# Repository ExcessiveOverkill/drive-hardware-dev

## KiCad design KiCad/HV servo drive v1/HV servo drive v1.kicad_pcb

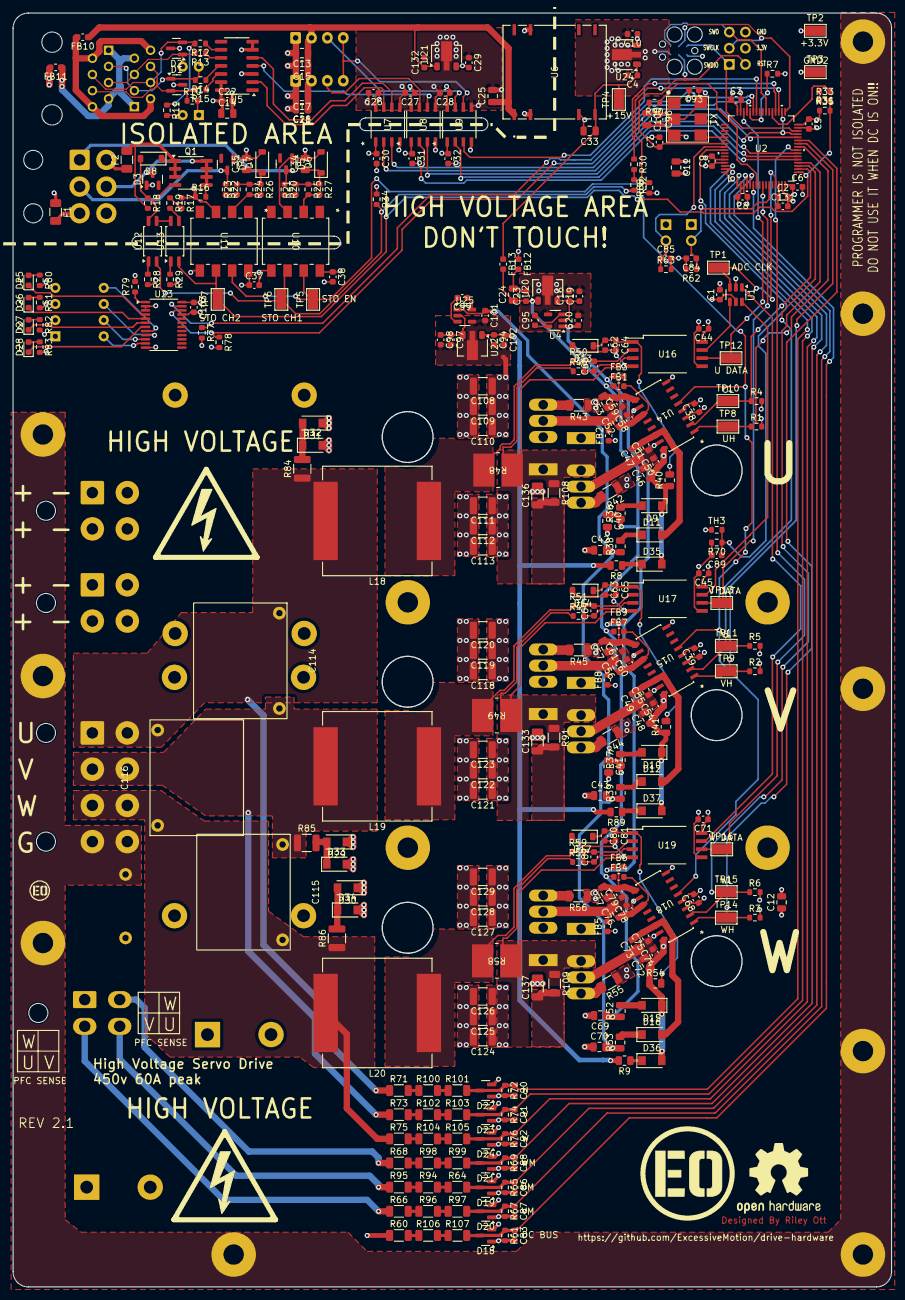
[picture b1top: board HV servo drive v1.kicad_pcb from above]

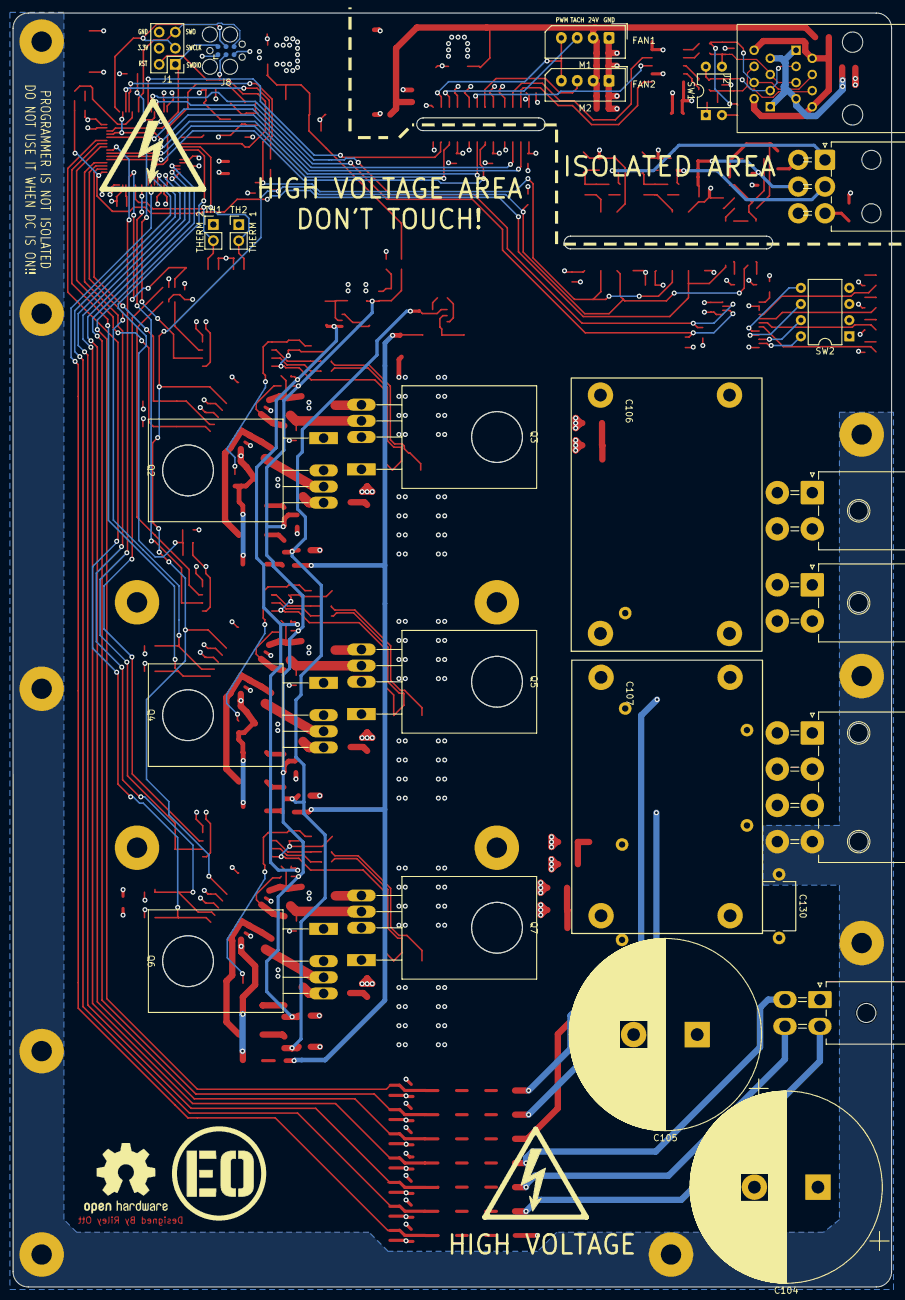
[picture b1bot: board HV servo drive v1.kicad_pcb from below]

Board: 4 copper layers, 138.2 x 200.4 mm, 371 parts (25 on the bottom side), 197 nets.

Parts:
C1, C3, C4, C5, C6, C7, C8, C9, C10, C16, C22, C23, C26, C27, C28, C29, C30, C31, C32, C36, C37, C38, C39, C44, C45, C50, C51, C54, C55, C58, C59, C60, C61, C64, C65, C68, C71, C74, C75, C78, C79, C81, C83, C86, C87, C88, C90, C91, C92, C93, C94, C96, C97, C103, C132: 0.1uf; C_0603_1608Metric
C2, C19, C20, C62, C63, C80, C84, C85, C89, C95, C98, C99, C101, C102, C131: 1uf; C_0603_1608Metric
C11, C12, C13, C14, C15, C17, C18, C21, C24, C25, C33, C34, C35, C40, C41, C42, C43, C46, C47, C48, C49, C52, C53, C56, C57, C69, C70, C72, C73, C76, C77, C100: 10uf; C_0805_2012Metric
C66, C67, C82: C; C_0603_1608Metric
C104, C105: 470uf; CP_Radial_D30.0mm_P10.00mm_SnapIn
C106, C107: 40uf; BUS CAP1
C108, C109, C110, C111, C112, C113, C118, C119, C120, C121, C122, C123, C124, C125, C126, C127, C128, C129: 47nf; C_1210_3225Metric
C114, C115, C116: 390pf; B326712L-SMD
C130: 220pf; C_Disc_D7.5mm_W5.0mm_P10.00mm
C133, C136, C137: 470pf; C_1206_3216Metric
D1, D2: SM712; SOT-23
D3, D4, D5, D18, D19, D20, D21, D22, D23, D24: BAT54SLT1G; SOT-23
D6, D7, D8, D13, D14, D17: BZT52C5V1; D_SOD-123
D9, D10, D11, D12, D15, D16, D29, D30, D31, D32, D33, D34, D35, D36, D37: RS1MLW; D_SOD-123W
D25, D26, D27, D28: LED; LED_0603_1608Metric
F1, F2: Polyfuse; Fuse_1206_3216Metric
FB1, FB2, FB3, FB4, FB5, FB6, FB7, FB8, FB9, FB10, FB11, FB12, FB13: 120 ohm; L_0603_1608Metric
H1, H2, H3, H4, H5, H6, H7, H8, H9, H10, H11, H12, H13: MountingHole; MountingHole_3.2mm_M3_Pad_TopBottom_LargeIsolation
J1: PROG; PinHeader_2x03_P2.54mm_Vertical
J2: E5908-0T0343-L; RJ45_E5908-0T0343-L
J3: STO; Molex_Mini-Fit_Jr_0455580003_2x03_P4.20mm_Horizontal
J4: PFC SENSE; Molex_Mini-Fit_Jr_5569-04A2_2x02_P4.20mm_Horizontal
J5: MOTOR; Molex_Mega-Fit_76825-0008_2x04_P5.70mm_Horizontal
J6, J7: DC BUS; Molex_Mega-Fit_76825-0004_2x02_P5.70mm_Horizontal
J8: Conn_ARM_SWD_TagConnect_TC2030; Tag-Connect_TC2030-IDC-FP_2x03_P1.27mm_Vertical
L18, L19, L20: 3.3uH; L_Vishay_IHLP-6767
M1, M2: Fan_4pin; Molex_SPOX_5267-04A_1x04_P2.50mm_Vertical
Q1: AO4421; SOIC-8_3.9x4.9mm_P1.27mm
Q2, Q3, Q4, Q5, Q6, Q7: G3R30MT12K; TO-247-4_Horizontal_TabUp
R1, R2, R3, R4, R5, R6, R7, R16, R18, R30, R31, R32, R33, R61, R62, R63, R65, R67, R69, R70, R72, R74, R76, R77, R78, R79, R88: 10k; R_0603_1608Metric
R8, R9, R36, R37, R38, R39, R52, R53, R89: 1; R_0805_2012Metric
R10, R11: 120; R_0603_1608Metric
R12, R13, R14, R15: 10; R_0603_1608Metric
R17, R19, R20, R21, R22, R23, R24, R25, R26, R27, R34, R35, R80, R81, R82, R83, R90: 1k; R_0603_1608Metric
R28, R29: 220; R_0603_1608Metric
R40, R41, R54: 820; R_0805_2012Metric
R42, R43, R44, R45, R55, R56, R91, R108, R109: 10; R_1206_3216Metric
R46, R47, R50, R51, R57, R59: 0; R_0603_1608Metric
R48, R49, R58: .005; RES_HCSM2818_STP
R60, R64, R66, R68, R71, R73, R75, R94, R95, R96, R97, R98, R99, R100, R101, R102, R103, R104, R105, R106, R107: 750k; R_1206_3216Metric
R84, R85, R86: 20; R_1210_3225Metric
SW1: DS01-254-L-02BE; DIP-4_W7.62mm
SW2: DS02C-254-1L-04BE; DIP-8_W7.62mm
TH1, TH2: Thermistor; PinHeader_1x02_P2.54mm_Vertical
TH3: Thermistor; R_0603_1608Metric
TP1, TP2, TP3, TP4, TP5, TP6, TP7, TP8, TP9, TP10, TP11, TP12, TP13, TP14, TP15, TP16: TestPoint; TestPoint_Pad_3.1x1.6mm
U1: PL133-37TC; SOT-23-6
U2: STM32F413RGT6; LQFP64-10x10mm
U4, U25: TPS60400DBV; SOT-23-5
U5: THVD1552DR; SOIC-14_3.9x8.7mm_P1.27mm
U6: NXJ2S2415MC-R7; NXJ2_24V_MUR
U7, U8, U9: ISO6721BQDRQ1; SOICN-8_LTF
U10, U11: 6N137; 6N137S_LTO
U12, U13: EL3H7; SOP-4_4.4x2.6mm_P1.27mm
U14, U15, U18: 2EDF8275FXUMA1; PG-DSO-16-11
U16, U17, U19: AMC1306M25DWVR; DWV0008A
U20, U21, U22: AP2205-50Y-13; SOT-89-3
U23: TCA9555PWR; TSSOP-24_4.4x7.8mm_P0.65mm
U24: AP2205-33Y-13; SOT-89-3
X1: FRETHE025; FR_3-3V

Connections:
5v_ISO: C14.1, C22.1, C26.1, C27.1, C28.1, C29.2, U5.13 (VCC), U5.14 (VCC), U7.8 (VCC2), U8.8 (VCC2), U9.8 (VCC2), U21.3 (VOUT)
24V_ISO: C13.1, C15.1, C17.1, C18.1, C21.1, C25.1, C132.1, FB10.1, M1.2 (+), M2.2 (+), U6.1 (+VIN), U21.1 (VIN)
+3.3V: C1.1, C3.1, C5.1, C6.1, C8.1, C9.1, C10.1, C11.1, C12.1, C30.1, C31.1, C32.1, C36.1, C37.1, C38.1, C39.1, C44.1, C45.1, C68.1, C71.1, C93.1, C103.1, D18.2 (K), D19.2 (K), D20.2 (K), D21.2 (K), D22.2 (K), D23.2 (K), D24.2 (K), J1.4, J8.1 (VCC), R28.2, R29.2, R34.1, R35.1, R77.2, R78.2, R79.2, R80.2, R81.2, R82.2, R83.2, TH1.1, TH2.1, TH3.1, TP2.1, U1.5 (V+), U2.13 (VDDA/VREF+), U2.19 (VDD), U2.32 (VDD), U2.48 (VDD), U2.64 (VDD), U7.1 (VCC1), U8.1 (VCC1), U9.1 (VCC1), U10.8 (VCC), U11.8 (VCC), U14.3 (VDDI), U14.8 (SLDON), U15.3 (VDDI), U15.8 (SLDON), U16.8 (DVDD), U17.8 (DVDD), U18.3 (VDDI), U18.8 (SLDON), U19.8 (DVDD), U23.24 (VCC), U24.3 (VOUT), X1.2 (OE), X1.6 (VCC)
+15V: C4.1, C33.1, FB13.1, TP4.1, U6.6 (+VOUT), U24.1 (VIN)
+15V_GATE: C23.1, C24.1, C40.1, C41.1, C69.1, FB1.1, FB4.1, FB7.1, FB13.2, R36.1, R37.1, R52.1, U20.1 (VIN)
-5V: C20.1, FB3.1, FB6.1, FB9.1, U4.1 (OUT)
BOARD_TEMP_1_ADC: C89.1, R70.1, TH3.2, U2.9 (PC1)
BOOT: R7.1, U2.60 (BOOT0)
DCBUS+: C42.1, C43.1, C70.1, C94.2, C97.2, C98.2, C101.2, C102.2, C104.1, C105.1, C106.1, C107.1, C108.1, C109.1, C110.1, C111.1, C112.1, C113.1, C118.1, C119.1, C120.1, C121.1, C122.1, C123.1, C124.1, C125.1, C126.1, C127.1, C128.1, C129.1, D29.1 (K), D30.1 (K), D31.1 (K), J6.1, J6.2, J7.1, J7.2, Q2.1 (D), Q4.1 (D), Q6.1 (D), R60.1, U22.2 (GND), U25.4 (GND)
DCBUS-: C104.2, C105.2, C106.2, C107.2, C108.2, C109.2, C110.2, C111.2, C112.2, C113.2, C118.2, C119.2, C120.2, C121.2, C122.2, C123.2, C124.2, C125.2, C126.2, C127.2, C128.2, C129.2, C130.2, C133.2, C136.2, C137.2, D32.2 (A), D33.2 (A), D34.2 (A), J6.3, J6.4, J7.3, J7.4, Q3.2 (S), Q5.2 (S), Q7.2 (S)
FAN_PWM: U2.58 (PB6), U9.3 (INB)
FAN_PWM_ISO: M1.4 (PWM), M2.4 (PWM), U9.6 (OUTB)
GND: C130.1, H1.1, H2.1, H3.1, H4.1, H5.1, H6.1, H7.1, H8.1, H9.1, J5.4, J5.8
GND1: C13.2, C14.2, C15.2, C17.2, C18.2, C21.2, C22.2, C25.2, C26.2, C27.2, C28.2, C29.1, C132.2, D1.3 (common), D2.3 (common), FB11.2, M1.1 (-), M2.1 (-), U5.3 (~RE), U5.6 (GND), U5.7 (GND), U6.2 (-VIN), U6.11 (-VIN), U7.5 (GND2), U8.5 (GND2), U9.5 (GND2), U21.2 (GND)
GND2: C1.2, C2.2, C3.2, C4.2, C5.2, C6.2, C7.2, C8.2, C9.2, C10.2, C11.2, C12.2, C30.2, C31.2, C32.2, C33.2, C36.2, C37.2, C38.2, C39.2, C44.2, C45.2, C68.2, C71.2, C83.2, C84.2, C85.2, C86.2, C87.2, C88.2, C89.2, C90.2, C91.2, C92.2, C93.2, C96.2, C100.2, C103.2, C131.2, D18.1 (A), D19.1 (A), D20.1 (A), D21.1 (A), D22.1 (A), D23.1 (A), D24.1 (A), FB12.1, J1.6, J8.5 (GND), R1.2, R2.2, R3.2, R4.2, R5.2, R6.2, R7.2, R61.2, R62.2, R63.2, R65.2, R67.2, R69.2, R70.2, R72.2, R74.2, R76.2, R88.1, SW2.1, SW2.2, SW2.3, SW2.4, TP3.1, U1.2 (GND), U2.12 (VSSA/VREF-), U2.18 (VSS), U2.31 (VSS), U2.47 (VSS), U2.63 (VSS), U6.5 (-VOUT), U7.4 (GND1), U8.4 (GND1), U9.4 (GND1), U10.5 (GND), U11.5 (GND), U14.4 (GNDI), U15.4 (GNDI), U16.5 (DGND), U17.5 (DGND), U18.4 (GNDI), U19.5 (DGND), U23.2 (A1), U23.3 (A2), U23.12 (GND), U23.21 (A0), U24.2 (GND), X1.3 (GND)
GND3: C16.2, C19.2, C20.2, C23.2, C24.2, C40.2, C41.2, C69.2, FB2.1, FB5.1, FB8.1, FB12.2, U4.4 (GND), U20.2 (GND)
HEATSINK_TEMP_1_ADC: C84.1, R62.1, TH1.2, U2.27 (PB1)
HEATSINK_TEMP_2_ADC: C85.1, R63.1, TH2.2, U2.8 (PC0)
unnamed: C133.1, R91.2
unnamed: C136.1, R108.2
unnamed: C137.1, R109.2
unnamed: C34.1, D6.1 (K), R21.2, R25.1, R27.1
unnamed: C35.1, D7.1 (K), R23.2, R24.1, R26.1
unnamed: D8.2 (A), Q1.4 (G), R18.1, U12.4
unnamed: D9.2 (A), R36.2
unnamed: D10.2 (A), R37.2
unnamed: C48.1, C54.1, D10.1 (K), D37.2 (A), R41.1, U15.16 (VDDA)
unnamed: C47.2, C51.2, D11.2 (A), U14.14 (GNDA)
unnamed: D11.1 (K), R38.2
unnamed: C49.2, C55.2, D12.2 (A), U15.14 (GNDA)
unnamed: D12.1 (K), R39.2
unnamed: C62.2, C64.2, D13.2 (A), Q2.2 (S), Q3.1 (D), R46.1, R48.1, R108.1, U16.4 (AGND)
unnamed: C62.1, C64.1, D13.1 (K), R40.2, U16.1 (AVDD)
unnamed: C63.2, C65.2, D14.2 (A), Q4.2 (S), Q5.1 (D), R47.1, R49.1, R91.1, U17.4 (AGND)
unnamed: C63.1, C65.1, D14.1 (K), R41.2, U17.1 (AVDD)
unnamed: D15.2 (A), R52.2
unnamed: C72.1, C74.1, D15.1 (K), D36.2 (A), R54.1, U18.16 (VDDA)
unnamed: C73.2, C75.2, D16.2 (A), U18.14 (GNDA)
unnamed: D16.1 (K), R53.2
unnamed: C80.2, C81.2, D17.2 (A), Q6.2 (S), Q7.1 (D), R57.1, R58.1, R109.1, U19.4 (AGND)
unnamed: C80.1, C81.1, D17.1 (K), R54.2, U19.1 (AVDD)
unnamed: D25.2 (A), R80.1
unnamed: D25.1 (K), U23.4 (P00)
unnamed: D26.2 (A), R81.1
unnamed: D26.1 (K), U23.5 (P01)
unnamed: D27.2 (A), R82.1
unnamed: D27.1 (K), U23.6 (P02)
unnamed: D28.2 (A), R83.1
unnamed: D28.1 (K), U23.7 (P03)
unnamed: D29.2 (A), D33.1 (K), R85.2
unnamed: D30.2 (A), D34.1 (K), R86.2
unnamed: D31.2 (A), D32.1 (K), R84.2
unnamed: C46.1, C50.1, D9.1 (K), D35.2 (A), R40.1, U14.16 (VDDA)
unnamed: D35.1 (K), R8.1
unnamed: D36.1 (K), R9.1
unnamed: D37.1 (K), R89.1
unnamed: FB10.2, J2.1, J2.7
unnamed: FB11.1, J2.2, J2.8
unnamed: F1.2, J3.3
unnamed: F2.1, J3.4
unnamed: C46.2, C47.1, C50.2, C51.1, Q2.3 (DS)
unnamed: Q2.4 (G), R42.2
unnamed: C52.2, C53.1, C58.2, C59.1, FB2.2, Q3.3 (DS)
unnamed: Q3.4 (G), R43.2
unnamed: C48.2, C49.1, C54.2, C55.1, Q4.3 (DS)
unnamed: Q4.4 (G), R44.2
unnamed: C56.2, C57.1, C60.2, C61.1, FB8.2, Q5.3 (DS)
unnamed: Q5.4 (G), R45.2
unnamed: C72.2, C73.1, C74.2, C75.1, Q6.3 (DS)
unnamed: Q6.4 (G), R55.2
unnamed: C76.2, C77.1, C78.2, C79.1, FB5.2, Q7.3 (DS)
unnamed: Q7.4 (G), R56.2
unnamed: R10.2, SW1.1
unnamed: R11.2, SW1.2
unnamed: R17.2, R19.1
unnamed: R19.2, U13.3
unnamed: R20.2, R21.1
unnamed: R22.2, R23.1
unnamed: R28.1, U12.1
unnamed: R29.1, U13.1
unnamed: R30.2, R32.1
unnamed: R31.2, R33.1
unnamed: R64.1, R94.2
unnamed: R66.2, R96.1
unnamed: R68.2, R98.1
unnamed: R94.1, R95.2
unnamed: R96.2, R97.1
unnamed: R98.2, R99.1
unnamed: R71.2, R100.1
unnamed: R100.2, R101.1
unnamed: R73.2, R102.1
unnamed: R102.2, R103.1
unnamed: R75.2, R104.1
unnamed: R104.2, R105.1
unnamed: R60.2, R106.1
unnamed: R106.2, R107.1
unnamed: TP1.1, U1.3 (IN), U2.29 (PB10)
unnamed: C2.1, C131.1, U2.30 (VCAP_1)
unnamed: C95.1, U4.5 (C_{FLY+})
unnamed: C95.2, U4.3 (C_{FLY-})
unnamed: R15.1, U5.12 (A)
unnamed: R14.1, U5.11 (B)
unnamed: R12.1, U5.9 (Y)
unnamed: R13.1, U5.10 (Z)
unnamed: R25.2, R27.2, U10.2 (A)
unnamed: R24.2, R26.2, U11.2 (A)
unnamed: U12.3, U13.4
unnamed: C53.2, C59.2, FB3.2, U14.9 (GNDB)
unnamed: R42.1, U14.15 (OUTA)
unnamed: R43.1, U14.10 (OUTB)
unnamed: C52.1, C58.1, FB1.2, U14.11 (VDDB)
unnamed: C57.2, C61.2, FB9.2, U15.9 (GNDB)
unnamed: R44.1, U15.15 (OUTA)
unnamed: R45.1, U15.10 (OUTB)
unnamed: C56.1, C60.1, FB7.2, U15.11 (VDDB)
unnamed: C66.1, R46.2, U16.3 (AINN)
unnamed: C66.2, R50.2, U16.2 (AINP)
unnamed: C67.1, R47.2, U17.3 (AINN)
unnamed: C67.2, R51.2, U17.2 (AINP)
unnamed: C77.2, C79.2, FB6.2, U18.9 (GNDB)
unnamed: R55.1, U18.15 (OUTA)
unnamed: R56.1, U18.10 (OUTB)
unnamed: C76.1, C78.1, FB4.2, U18.11 (VDDB)
unnamed: C82.1, R57.2, U19.3 (AINN)
unnamed: C82.2, R59.2, U19.2 (AINP)
unnamed: C16.1, C19.1, U4.2 (IN), U20.3 (VOUT)
unnamed: C97.1, C98.1, U22.3 (VOUT), U25.2 (IN)
unnamed: SW2.5, U23.8 (P04)
unnamed: SW2.6, U23.9 (P05)
unnamed: SW2.7, U23.10 (P06)
unnamed: SW2.8, U23.11 (P07)
unnamed: R79.1, U23.1 (~INT)
unnamed: C99.1, U25.5 (C_{FLY+})
unnamed: C99.2, U25.3 (C_{FLY-})
unnamed: C96.1, C100.1, R90.2, X1.1 (VC)
OSC: U2.5 (PH0-OSC_IN), X1.4 (OUT)
RESET: C7.1, J1.2, J8.3 (~RESET), U2.7 (NRST)
RX: U2.45 (PA12), U2.50 (PA15), U7.2 (OUTA)
RX+: D1.2 (A2), J2.3, R10.1, R15.2
RX-: D1.1 (A1), J2.6, R14.2, SW1.4
RX_ISO: U5.2 (RO), U7.7 (INA)
SAFE GND: C34.2, C35.2, D3.1 (A), D4.1 (A), D5.1 (A), D6.2 (A), D7.2 (A), F1.1, R16.1, R17.1, U10.3 (C), U11.3 (C)
SDA: R77.1, U2.59 (PB7), U23.23 (SDA)
SDL: R78.1, U2.61 (PB8), U23.22 (SCL)
STO CH1: R32.2, R34.2, TP6.1, U10.6 (VO), U12.2, U14.5 (DISABLE), U15.5 (DISABLE), U18.5 (DISABLE)
STO CH1 FIELD: D5.3 (common), J3.1, R20.1
STO CH1 MCU FBK: R30.1, U2.52 (PC11)
STO CH2: R33.2, R35.2, TP7.1, U2.33 (PB12), U11.6 (VO), U13.2
STO CH2 FIELD: D4.3 (common), J3.2, R22.1
STO CH2 MCU FBK: R31.1, U2.53 (PC12)
STO EN: R88.2, TP5.1, U2.51 (PC10), U10.7 (EN), U11.7 (EN)
STO FBK 24V: D8.1 (K), F2.2, Q1.1 (S), Q1.2 (S), Q1.3 (S), R18.2
STO FBK OUT: D3.3 (common), J3.5, Q1.5 (D), Q1.6 (D), Q1.7 (D), Q1.8 (D), R16.2
SWCLK: J1.3, J8.4 (SWCLK), U2.49 (PA14)
SWDIO: J1.1, J8.2 (SWDIO), U2.46 (PA13)
SWO: J1.5, J8.6 (SWO), U2.55 (PB3)
TACH_1: U2.37 (PC6), U8.2 (OUTA)
TACH_1_ISO: M2.3 (Tacho), U8.7 (INA)
TACH_2: U2.38 (PC7), U9.2 (OUTA)
TACH_2_ISO: M1.3 (Tacho), U9.7 (INA)
TX: U2.44 (PA11), U7.3 (INB)
TX+: D2.2 (A2), J2.5, R11.1, R12.2
TX-: D2.1 (A1), J2.4, R13.2, SW1.3
TX_EN: U2.39 (PC8), U8.3 (INB)
TX_EN_ISO: U5.4 (DE), U8.6 (OUTB)
TX_ISO: U5.5 (DI), U7.6 (OUTB)
U: C114.2, C116.1, J5.1, J5.5, L18.2, R71.1, R84.1
UH: R1.1, TP8.1, U2.41 (PA8), U14.1 (INA)
UL: R4.1, TP10.1, U2.34 (PB13), U14.2 (INB)
UM: J4.4, R95.1
UM_ADC: C86.1, D19.3 (common), R64.2, R65.1, U2.20 (PA4)
U_: L18.1, R48.2, R50.1
U_ADC: C90.1, D22.3 (common), R72.1, R101.2, U2.14 (PA0)
U_CLOCK: U1.4 (OUT0), U16.7 (CLKIN)
U_DATA: TP12.1, U2.62 (PB9), U16.6 (DOUT)
V: C114.1, C115.2, J5.2, J5.6, L19.2, R73.1, R85.1
VBUS +15V: C94.1, C102.1, R8.2, R9.2, R89.2, U22.1 (VIN)
VBUS -5V: C42.2, C43.2, C70.2, C101.1, R38.1, R39.1, R53.1, U25.1 (OUT)
VBUS_ADC: C83.1, D18.3 (common), R61.1, R107.2, U2.22 (PA6)
VCXO_VC: R90.1, U2.23 (PA7)
VH: R2.1, TP9.1, U2.42 (PA9), U15.1 (INA)
VL: R5.1, TP11.1, U2.35 (PB14), U15.2 (INB)
VM: J4.2, R66.1
VM_ADC: C87.1, D20.3 (common), R67.1, R97.2, U2.21 (PA5)
V_: L19.1, R49.2, R51.1
V_ADC: C91.1, D23.3 (common), R74.1, R103.2, U2.15 (PA1)
V_CLOCK: U1.6 (OUT2), U17.7 (CLKIN)
V_DATA: TP13.1, U2.25 (PC5), U17.6 (DOUT)
W: C115.1, C116.2, J5.3, J5.7, L20.2, R75.1, R86.1
WH: R3.1, TP14.1, U2.43 (PA10), U18.1 (INA)
WL: R6.1, TP15.1, U2.36 (PB15), U18.2 (INB)
WM: J4.3, R68.1
WM_ADC: C88.1, D21.3 (common), R69.1, R99.2, U2.17 (PA3)
W_: L20.1, R58.2, R59.1
W_ADC: C92.1, D24.3 (common), R76.1, R105.2, U2.16 (PA2)
W_CLOCK: U1.1 (OUT1), U19.7 (CLKIN)
W_DATA: TP16.1, U2.40 (PC9), U19.6 (DOUT)

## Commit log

2024-03-11 KiCad 8.0 update
2024-04-11 Added current sensor KiCad project
2024-04-19 start rev 2 changes
    fix component references, fix rj45 and dc-dc converter footprints, add RLC filters on all power connectors, add more mounting holes
2024-04-23 add STO enable pulldown for MCU
2024-04-26 round PCb edges
2025-04-02 add heatsink files
2025-09-05 update to rev 2.1
    basically the same version as in the FOC youtube video, with some minor issues fixed
2025-09-05 add reverse protection diodes to gate supply
